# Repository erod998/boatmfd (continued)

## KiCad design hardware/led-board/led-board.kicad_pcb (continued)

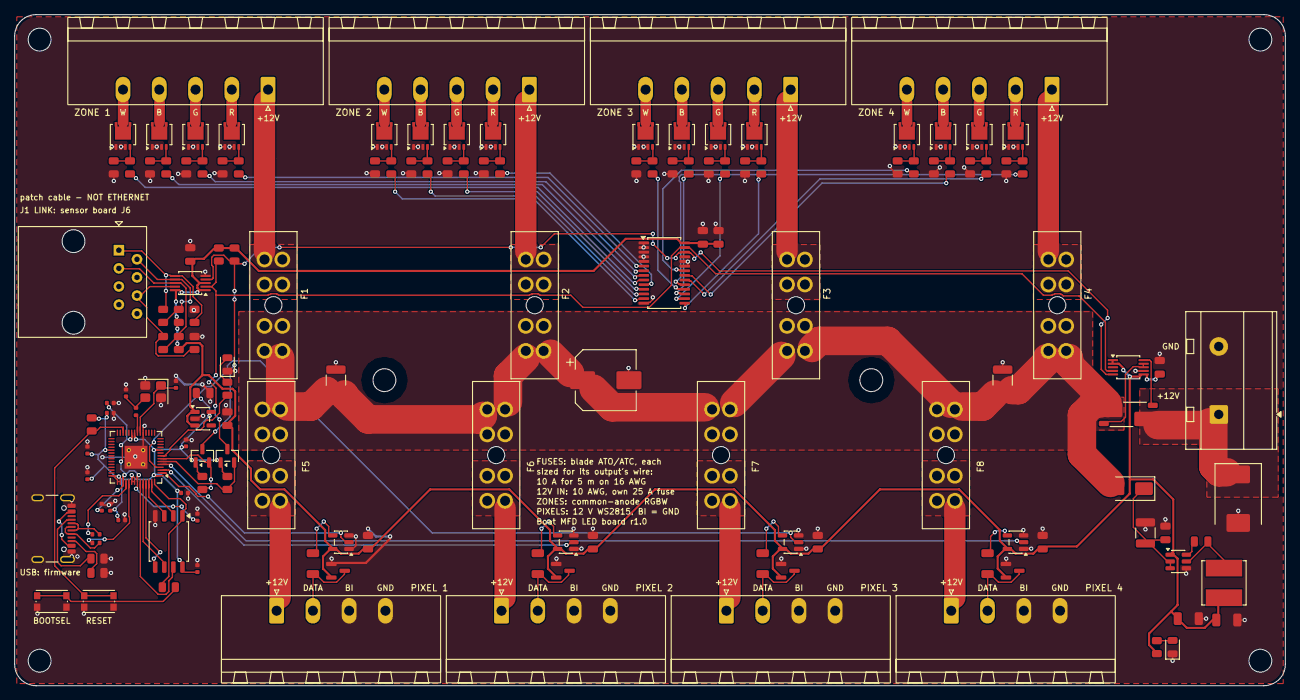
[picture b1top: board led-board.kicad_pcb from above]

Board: 2 copper layers, 178.0 x 94.0 mm, 153 parts (0 on the bottom side), 107 nets.

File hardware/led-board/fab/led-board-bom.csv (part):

Comment,Designator,Footprint,MPN,Qty,Mount,Note
100n,"C1,C5,C11,C12,C14,C15,C16,C17,C18",0805,CL21B104KBCNNNC,9,SMD,"U1 decoupling; U5 decoupling; U6 input, high frequency; U6 bootstrap; U7 decoupling; U8 decoupling; U9 decoupling; U10 decoupling; U4 decoupling"
22u,"C13,C19",1206,CL31A226KAHNNNE,2,SMD,U6 output
100n,"C20,C23,C24,C25,C26,C27,C28,C31,C32",0402,CL05B104KO5NNNC,9,SMD,"U3 decoupling; U2 IOVDD (pin 1); U2 IOVDD (pin 10); U2 IOVDD (pin 22); U2 IOVDD (pin 33); U2 IOVDD and ADC_AVDD (pins 42, 43); U2 USB_VDD and IOVDD (pins 48, 49); U2 DVDD (pin 23); U2 DVDD (pin 50)"
15p,"C21,C22",0402,CL05C150JB5NNNC,2,SMD,crystal load
1u,"C29,C30",0402,CL05A105KA5NQNC,2,SMD,U2 VREG_VIN (pin 44); U2 VREG_VOUT (pin 45): the 1.1 V core supply
10u,C34,0805,CL21A106KAYNNNE,1,SMD,"U11 output, the 3.3 V bulk"
1u,"C6,C33",0805,CL21B105KAFNNNE,2,SMD,U5 decoupling; U11 input
100u 35V,C7,CP,EEE-FK1V101P,1,SMD,"12 V bulk: the PWM's current steps, and damping for the feed wire"
10u,"C8,C9,C10",1210,CL32B106KBJNNNE,3,SMD,"12 V bypass, zone side; 12 V bypass, pixel side; U6 input (50 V)"
SMCJ18A,D1,SMC,SMCJ18A,1,SMD,1500 W surge clamp on the 12 V input (18 V stand-off)
SS14,D2,SMA,SS14,1,SMD,reverse polarity protection for the logic supply
BAT54S,"D3,D4,D5,D6",SOT-23,"BAT54S,215",4,SMD,clamps J7's data line between GND and 5 V; clamps J8's data line between GND and 5 V; clamps J9's data line between GND and 5 V; clamps J10's data line between GND and 5 V
green,D7,LED,LTST-C171GKT,1,SMD,lit when the board has 12 V
yellow,D8,LED,LTST-C171YKT,1,SMD,the RP2040's status: blinks while its firmware runs
USB,J11,USB_C_Receptacle_GCT_USB4105-xx-A_16P_TopMnt_Horizontal,GCT USB4105-GF-A,1,SMD,firmware loading only (VBUS unused: the board must have its 12 V)
6.8u,L1,L,SRN6045TA-6R8M,1,SMD,U6's inductor
BUK9M7R2-40E,"Q1,Q2,Q3,Q4,Q5,Q6,Q7,Q8,Q9,Q10,Q11,Q12,Q13,Q14,Q15,Q16",LFPAK33,BUK9M7R2-40EX,16,SMD,zone 1 R: PCA9685 output 0; zone 1 G: PCA9685 output 1; zone 1 B: PCA9685 output 2; zone 1 W: PCA9685 output 3; zone 2 R: PCA9685 output 4; zone 2 G: PCA9685 output 5; zone 2 B: PCA9685 output 6; zone 2 W: PCA9685 output 7; zone 3 R: PCA9685 output 8; zone 3 G: PCA9685 output 9; zone 3 B: PCA9685 output 10; zone 3 W: PCA9685 output 11; zone 4 R: PCA9685 output 12; zone 4 G: PCA9685 output 13; zone 4 B: PCA9685 output 14; zone 4 W: PCA9685 output 15
BSS138,"Q17,Q18",SOT-23,BSS138,2,SMD,"SDA level shift, 3.3 V to 5 V; SCL level shift, 3.3 V to 5 V"
100,"R1,R2,R3,R4,R5,R6,R7,R8,R9,R10,R11,R12,R13,R14,R15,R16",0805,RC0805FR-07100RL,16,SMD,gate resistor
47k,"R17,R18,R19,R20,R21,R22,R23,R24,R25,R26,R27,R28,R29,R30,R31,R32",0805,RC0805FR-0747KL,16,SMD,gate pull-down
620,"R33,R35,R36,R38",0805,RC0805FR-07620RL,4,SMD,link SCL pair: bias (pull-up); link SCL pair: bias (pull-down); link SDA pair: bias (pull-up); link SDA pair: bias (pull-down)
120,"R34,R37",0805,RC0805FR-07120RL,2,SMD,link SCL pair: termination; link SDA pair: termination
4.7k,"R39,R40",0805,RC0805FR-074K7L,2,SMD,"I2C pull-up, 5 V side"
10k,"R41,R42,R49",0805,RC0805FR-0710KL,3,SMD,"I2C pull-up, RP2040 side; RUN pull-up"
330,"R43,R44,R45,R46",1206,RC1206FR-07330RL,4,SMD,J7 data series resistor; J8 data series resistor; J9 data series resistor; J10 data series resistor
1m,R47,2512 (4-terminal),WSK25121L000FEA,1,SMD,"1 mOhm, 1 W, four-terminal: 20 A makes 20 mV and 0.4 W"
1k,R48,0402,RC0402FR-071KL,1,SMD,limits the crystal's drive
1k,"R50,R55",0805,RC0805FR-071KL,2,SMD,BOOTSEL button to the flash's chip select; status LED
27,"R51,R52",0402,RC0402FR-0727RL,2,SMD,USB series resistor
5.1k,"R53,R54",0805,RC0805FR-075K1L,2,SMD,USB-C: identifies the board as a device
2.2k,R56,0805,RC0805FR-072K2L,1,SMD,power LED
BOOTSEL,SW1,SW,KMR221GLFS,1,SMD,"held during reset: U2 starts as a USB drive, to load firmware"
RESET,SW2,SW,KMR221GLFS,1,SMD,resets U2
PCA9615DP,U1,TSSOP-10,"PCA9615DP,118",1,SMD,"differential I2C from the RJ45, back to plain I2C"
AP2112K-3.3,U11,SOT-23-5,AP2112K-3.3TRG1,1,SMD,3.3 V for the RP2040 and its flash
RP2040,U2,QFN-56-1EP,RP2040,1,SMD,runs the addressable outputs; I2C target at 0x30
W25Q16JV,U3,SOIC-8,W25Q16JVSSIQ,1,SMD,U2's program (2 MB QSPI flash)
INA226,U4,TSSOP-10,INA226AIDGSR,1,SMD,"the board's current and voltage, I2C address 0x45"
PCA9685PW,U5,TSSOP-28,"PCA9685PW,118",1,SMD,"16 PWM channels, I2C address 0x40"
AP63205,U6,TSOT-23-6,AP63205WU-7,1,SMD,"5 V for the logic, 2 A buck (about 100 mA used)"
74AHCT1G125,"U7,U8,U9,U10",SOT-23-5,SN74AHCT1G125DBVR,4,SMD,pixel output 1: 3.3 V data to 5 V; pixel output 2: 3.3 V data to 5 V; pixel output 3: 3.3 V data to 5 V; pixel output 4: 3.3 V data to 5 V
12MHz,Y1,3225-4Pin,ABM8-272-T3,1,SMD,"U2's clock: the crystal Raspberry Pi specify, with its 15 pF loads and 1k in XOUT"
ATO,"F1,F2,F3,F4,F5,F6,F7,F8",FuseHolder_Blade_ATO_Littelfuse_FLR_178.6165,"Littelfuse 178.6165.0002 (ATO/ATC holder, 30 A)",8,THT (hand solder),zone 1's fuse: a standard blade (ATO/ATC) fuse sized for the strip's wire -- 10 A for 5 m of RGBW on 16 AWG; zone 2's fuse: a standard blade (ATO/ATC) fuse sized for the strip's wire -- 10 A for 5 m of RGBW on 16 AWG; zone 3's fuse: a standard blade (ATO/ATC) fuse sized for the strip's wire -- 10 A for 5 m of RGBW on 16 AWG; zone 4's fuse: a standard blade (ATO/ATC) fuse sized for the strip's wire -- 10 A for 5 m of RGBW on 16 AWG; J7's fuse: a standard blade (ATO/ATC) fuse -- 10 A for 5 m of WS2815 on 16 AWG; J8's fuse: a standard blade (ATO/ATC) fuse -- 10 A for 5 m of WS2815 on 16 AWG; J9's fuse: a standard blade (ATO/ATC) fuse -- 10 A for 5 m of WS2815 on 16 AWG; J10's fuse: a standard blade (ATO/ATC) fuse -- 10 A for 5 m of WS2815 on 16 AWG
LINK,J1,RJ45_Amphenol_54602-x08_Horizontal,Amphenol 54602-908LF,1,THT (hand solder),to the sensor board's J6: a straight-through Cat5e/Cat6 patch cable. NOT Ethernet: never plug either end into a network switch or a PoE injector
PIXEL 4,J10,"PhoenixContact_MSTB_2,5_4-GF-5,08_1x04_P5.08mm_Horizontal_ThreadedFlange","Phoenix Contact 1776524 (MSTB 2,5/ 4-GF-5,08); plug 1778001 (MSTB 2,5/ 4-STF-5,08)",1,THT (hand solder),"12 V addressable strip (WS2815...): 1 +12V, 2 DATA, 3 BI (ground), 4 GND; 12 A per pin"
12V IN,J2,TerminalBlock_MetzConnect_Type703_RT10N02HGLU_1x02_P9.52mm_Horizontal,METZ CONNECT RT10N02HGLU,1,THT (hand solder),"the strips' 12 V, 20 A (the terminal is rated 24 A, 10 AWG), from its own 25 A fuse"
ZONE 1,J3,"PhoenixContact_MSTB_2,5_5-GF-5,08_1x05_P5.08mm_Horizontal_ThreadedFlange","Phoenix Contact 1776537 (MSTB 2,5/ 5-GF-5,08); plug 1778014 (MSTB 2,5/ 5-STF-5,08)",1,THT (hand solder),"RGBW strip, common anode: 1 +12V, 2 R, 3 G, 4 B, 5 W (PCA9685 outputs 0-3); 12 A per pin"
ZONE 2,J4,"PhoenixContact_MSTB_2,5_5-GF-5,08_1x05_P5.08mm_Horizontal_ThreadedFlange","Phoenix Contact 1776537 (MSTB 2,5/ 5-GF-5,08); plug 1778014 (MSTB 2,5/ 5-STF-5,08)",1,THT (hand solder),"RGBW strip, common anode: 1 +12V, 2 R, 3 G, 4 B, 5 W (PCA9685 outputs 4-7); 12 A per pin"
ZONE 3,J5,"PhoenixContact_MSTB_2,5_5-GF-5,08_1x05_P5.08mm_Horizontal_ThreadedFlange","Phoenix Contact 1776537 (MSTB 2,5/ 5-GF-5,08); plug 1778014 (MSTB 2,5/ 5-STF-5,08)",1,THT (hand solder),"RGBW strip, common anode: 1 +12V, 2 R, 3 G, 4 B, 5 W (PCA9685 outputs 8-11); 12 A per pin"
ZONE 4,J6,"PhoenixContact_MSTB_2,5_5-GF-5,08_1x05_P5.08mm_Horizontal_ThreadedFlange","Phoenix Contact 1776537 (MSTB 2,5/ 5-GF-5,08); plug 1778014 (MSTB 2,5/ 5-STF-5,08)",1,THT (hand solder),"RGBW strip, common anode: 1 +12V, 2 R, 3 G, 4 B, 5 W (PCA9685 outputs 12-15); 12 A per pin"
PIXEL 1,J7,"PhoenixContact_MSTB_2,5_4-GF-5,08_1x04_P5.08mm_Horizontal_ThreadedFlange","Phoenix Contact 1776524 (MSTB 2,5/ 4-GF-5,08); plug 1778001 (MSTB 2,5/ 4-STF-5,08)",1,THT (hand solder),"12 V addressable strip (WS2815...): 1 +12V, 2 DATA, 3 BI (ground), 4 GND; 12 A per pin"
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
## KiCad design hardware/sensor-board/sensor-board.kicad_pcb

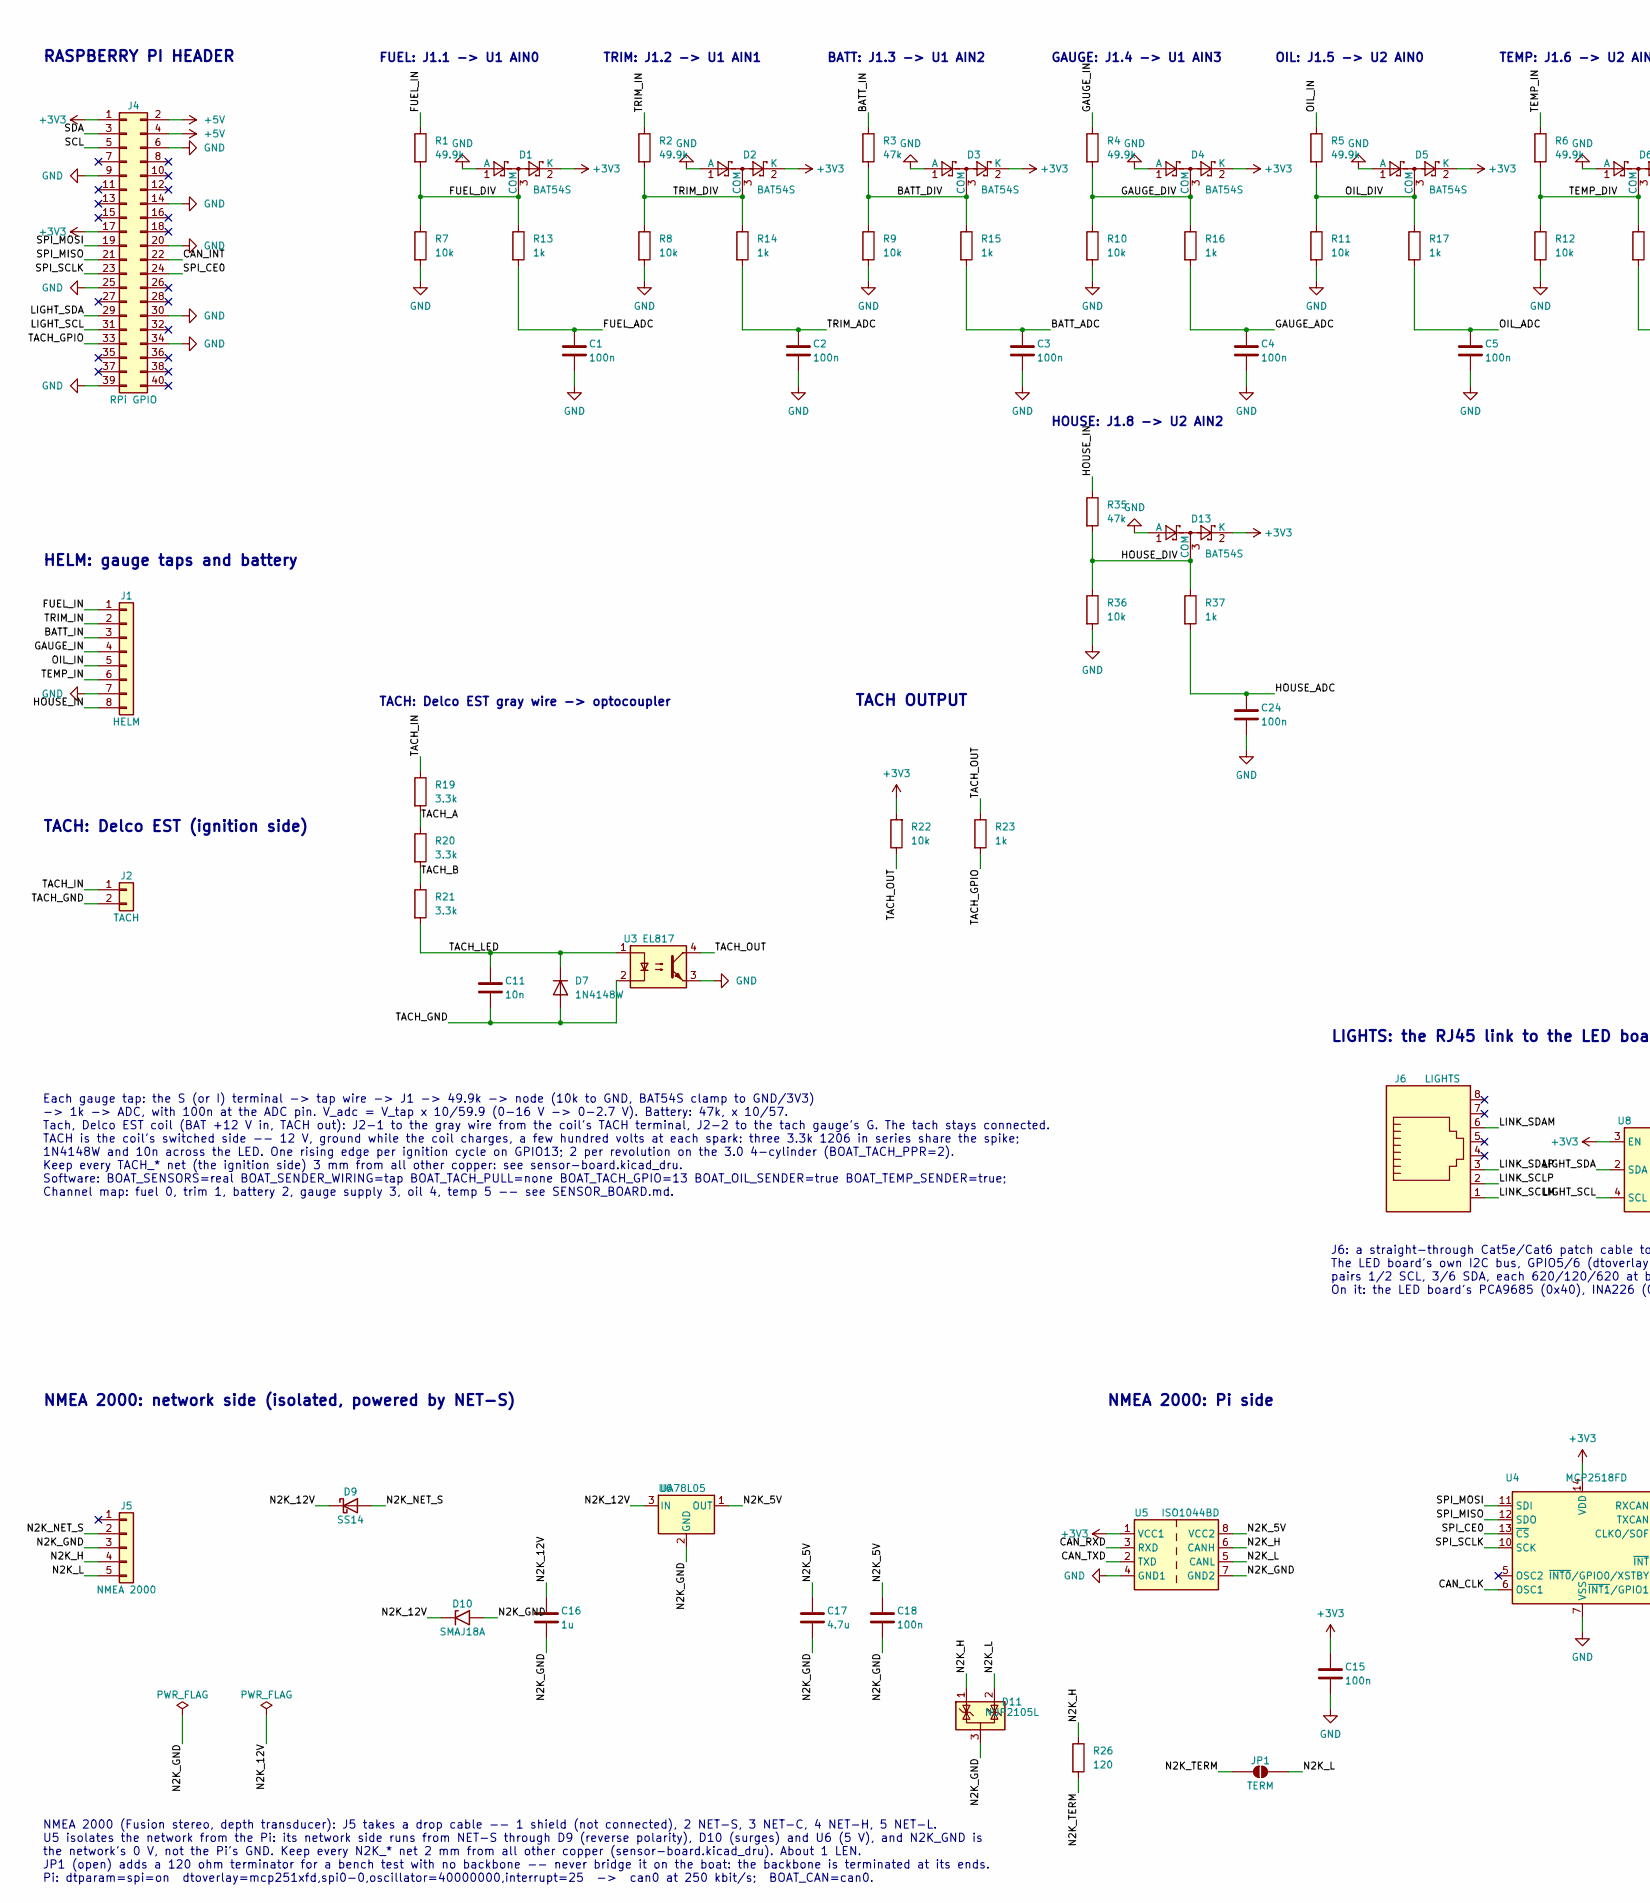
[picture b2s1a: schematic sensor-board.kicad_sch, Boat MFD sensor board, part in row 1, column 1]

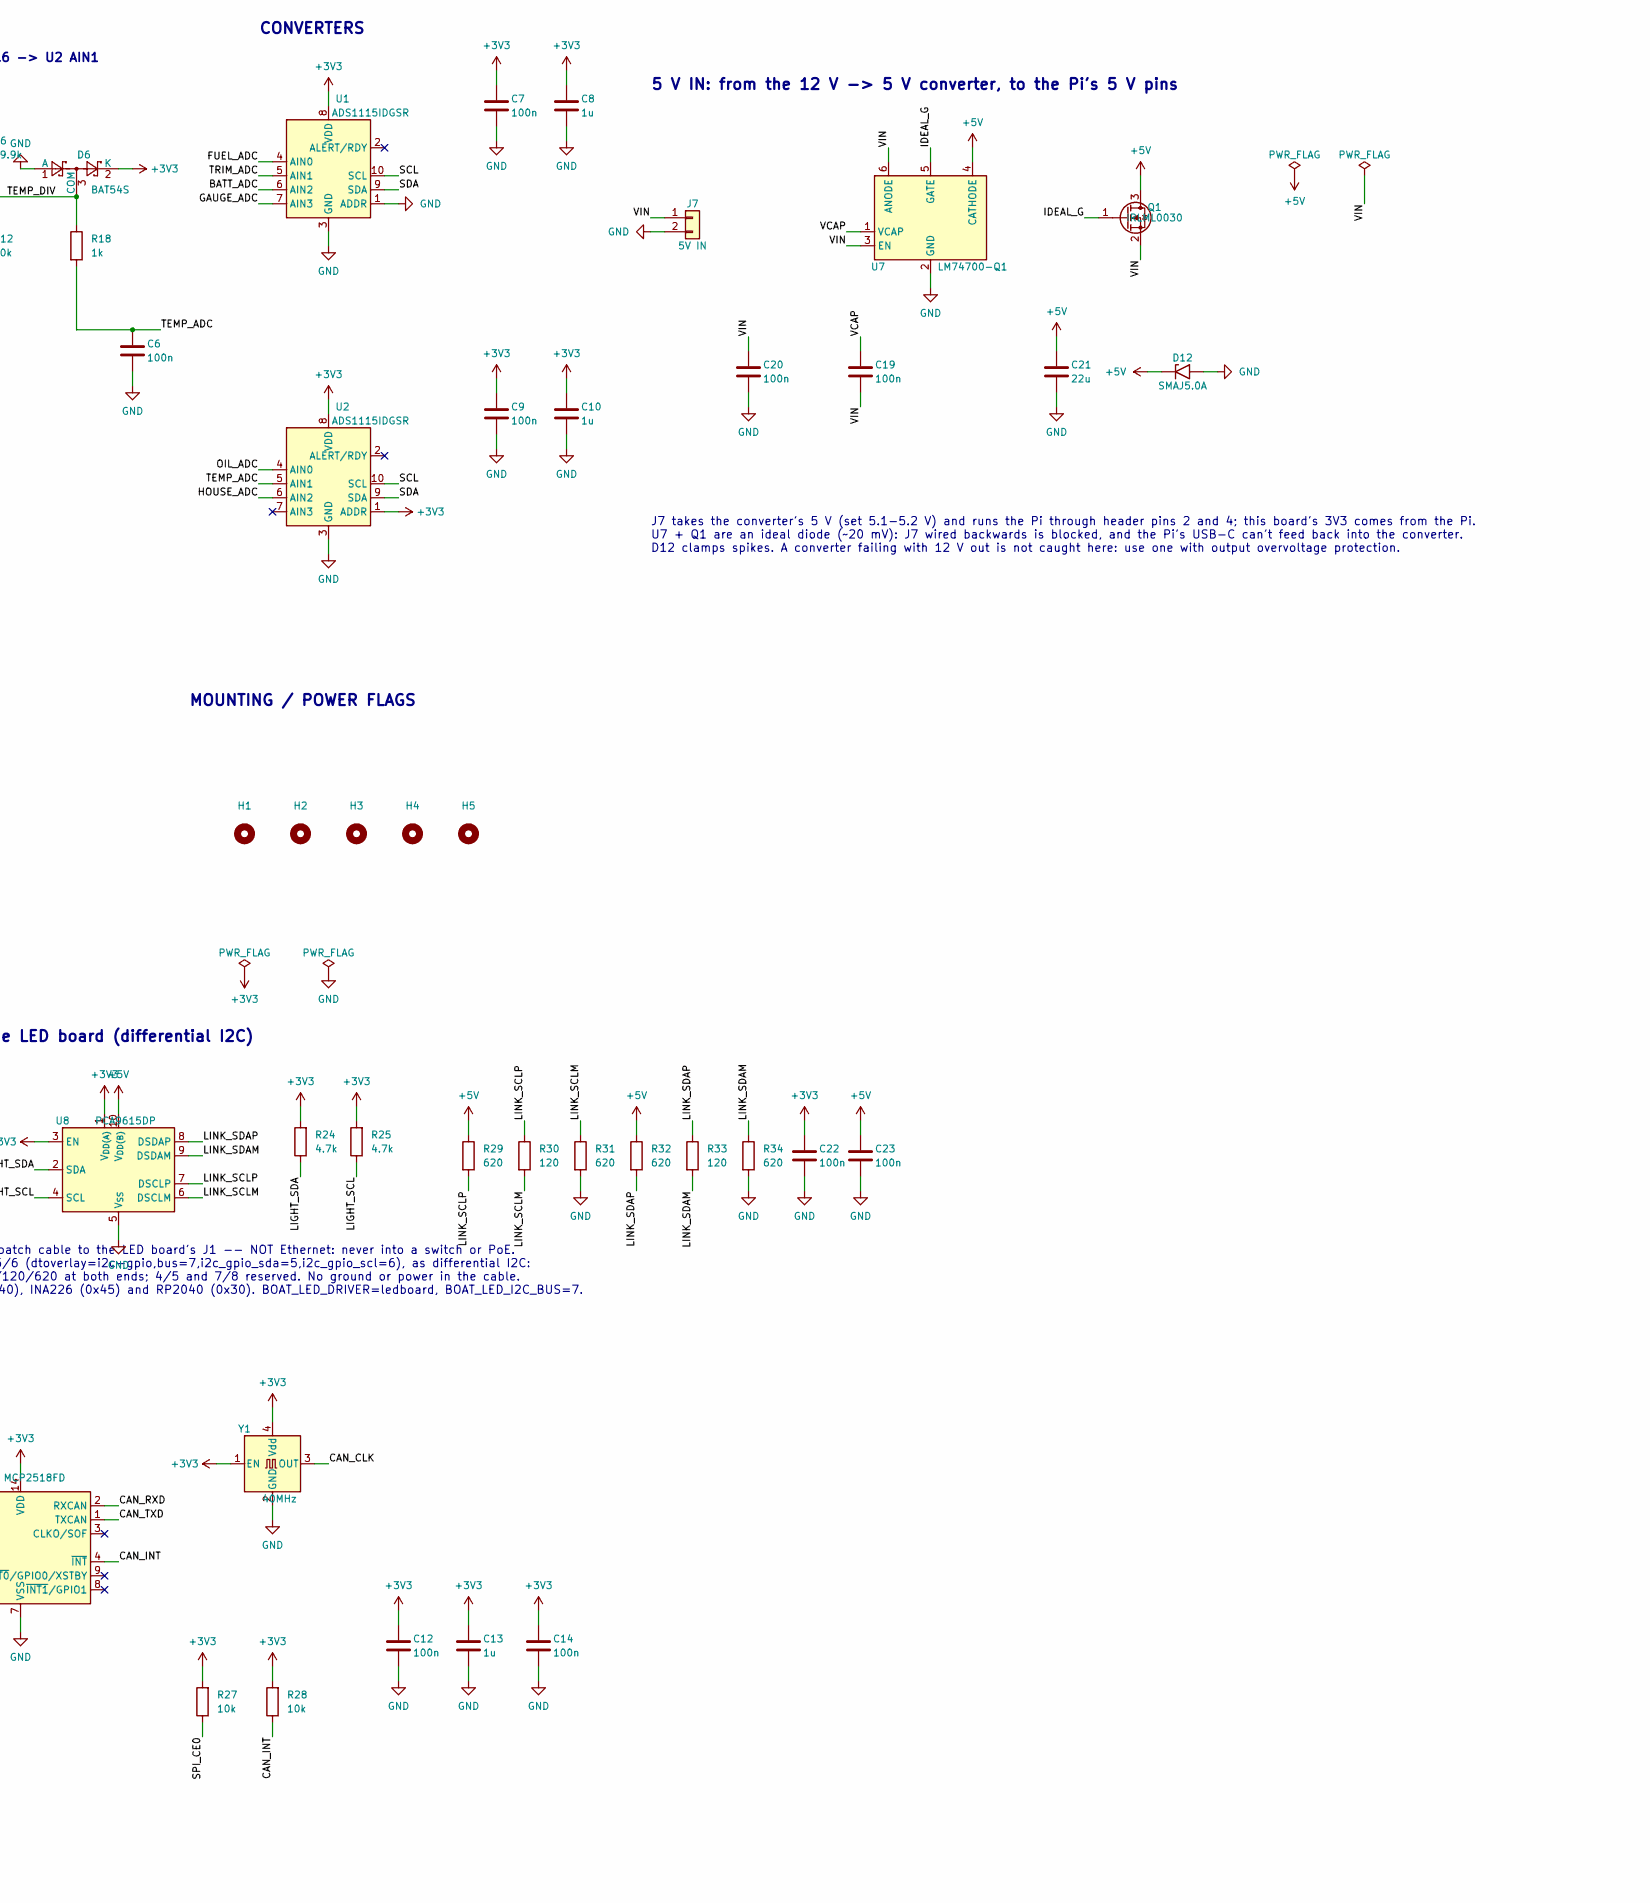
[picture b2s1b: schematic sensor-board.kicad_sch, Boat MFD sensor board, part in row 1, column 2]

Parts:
C1, C2, C3, C4, C5, C6, C7, C9, C12, C14, C15, C18, C19, C20, C24: 100n; C_0805_2012Metric_NoSilk; MPN CL21B104KBCNNNC
C8, C10, C13: 1u; C_0805_2012Metric_NoSilk; MPN CL21B105KAFNNNE
C11: 10n; C_0805_2012Metric_NoSilk; MPN CL21B103KBANNNC
C16: 1u; C_1206_3216Metric_NoSilk; MPN CL31B105KBHNNNE
C17: 4.7u; C_0805_2012Metric_NoSilk; MPN CL21A475KAQNNNE
C21: 22u; C_1206_3216Metric_NoSilk; MPN CL31A226KAHNNNE
C22, C23: 100n; C_0402_1005Metric_NoSilk; MPN CL05B104KO5NNNC
D1, D2, D3, D4, D5, D6, D13: BAT54S; SOT-23_NoSilk; MPN BAT54S,215
D7: 1N4148W; D_SOD-123; MPN 1N4148W-7-F
D9: SS14; D_SMA; MPN SS14
D10: SMAJ18A; D_SMA; MPN SMAJ18A
D11: NUP2105L; SOT-23_NoSilk; MPN NUP2105LT1G
D12: SMAJ5.0A; D_SMA; MPN SMAJ5.0A
H1, H2, H3, H4, H5: MountingHole; MountingHole_2.7mm_M2.5
J1: HELM; PhoenixContact_MC_1,5_8-GF-3.81_1x08_P3.81mm_Horizontal_Thr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; MPN Phoenix Contact 1827923 (MC 1,5/ 8-GF-3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
J2: TACH; PhoenixContact_MC_1,5_2-GF-3.81_1x02_P3.81mm_Horizontal_Thr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; MPN Phoenix Contact 1827868 (MC 1,5/ 2-GF-3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
J4: RPi GPIO; PinSocket_2x20_P2.54mm_Vertical; MPN 2x20 female stacking header, 2.54 mm, e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
J5: NMEA 2000; PhoenixContact_MC_1,5_5-GF-3.81_1x05_P3.81mm_Horizontal_Thr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; MPN Phoenix Contact 1827897 (MC 1,5/ 5-GF-3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
J6: LIGHTS; RJ45_Amphenol_54602-x08_Horizontal; MPN Amphenol 54602-908LF
J7: 5V IN; PhoenixContact_MC_1,5_2-GF-3.81_1x02_P3.81mm_Horizontal_Thr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; MPN Phoenix Contact 1827868 (MC 1,5/ 2-GF-3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
JP1: TERM; SolderJumper-2_P1.3mm_Open_RoundedPad1.0x1.5mm
Q1: IRLML0030; SOT-23; MPN IRLML0030TRPBF
R1, R2, R4, R5, R6: 49.9k; R_1206_3216Metric_NoSilk; MPN RC1206FR-0749K9L
R3, R35: 47k; R_1206_3216Metric_NoSilk; MPN RC1206FR-0747KL
R7, R8, R9, R10, R11, R12, R22, R27, R28, R36: 10k; R_0805_2012Metric_NoSilk; MPN RC0805FR-0710KL
R13, R14, R15, R16, R17, R18, R23, R37: 1k; R_0805_2012Metric_NoSilk; MPN RC0805FR-071KL
R19, R20, R21: 3.3k; R_1206_3216Metric_NoSilk; MPN RC1206FR-073K3L
R24, R25: 4.7k; R_0805_2012Metric_NoSilk; MPN RC0805FR-074K7L
R26: 120; R_0805_2012Metric_NoSilk; MPN RC0805FR-07120RL
R29, R31, R32, R34: 620; R_0402_1005Metric_NoSilk; MPN RC0402FR-07620RL
R30, R33: 120; R_0402_1005Metric_NoSilk; MPN RC0402FR-07120RL
U1, U2: ADS1115IDGSR; TSSOP-10_3x3mm_P0.5mm; MPN ADS1115IDGSR
U3: EL817; SMDIP-4_W9.53mm; MPN EL817S1(C)(TU)-F
U4: MCP2518FD; SOIC-14_3.9x8.7mm_P1.27mm; MPN MCP2518FDT-E/SL
U5: ISO1044BD; SOIC-8_3.9x4.9mm_P1.27mm; MPN ISO1044BDR
U6: UA78L05; SOT-89-3; MPN UA78L05ACPK
U7: LM74700-Q1; SOT-23-6; MPN LM74700QDBVRQ1
U8: PCA9615DP; TSSOP-10_3x3mm_P0.5mm; MPN PCA9615DP,118
Y1: 40MHz; Oscillator_SMD_Abracon_ASE-4Pin_3.2x2.5mm; MPN ASE-40.000MHZ-L-C-T

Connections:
+3V3: C7.1, C8.1, C9.1, C10.1, C12.1, C13.1, C14.1, C15.1, C22.1, D1.2 (K), D2.2 (K), D3.2 (K), D4.2 (K), D5.2 (K), D6.2 (K), D13.2 (K), J4.1, J4.17, R22.2, R24.2, R25.2, R27.2, R28.2, U1.8 (VDD), U2.1 (ADDR), U2.8 (VDD), U4.14 (VDD), U5.1 (VCC1), U8.1 (V_{DD(A)}), U8.3 (EN), Y1.1 (EN), Y1.4 (Vdd)
+5V: C21.1, C23.1, D12.1 (A1), J4.2, J4.4, Q1.3 (D), R29.1, R32.1, U7.4 (CATHODE), U8.10 (V_{DD(B)})
/BATT_ADC: C3.1, R15.2, U1.6 (AIN2)
/BATT_DIV: D3.3 (COM), R3.2, R9.1, R15.1
/BATT_IN: J1.3, R3.1
/CAN_CLK: U4.6 (OSC1), Y1.3 (OUT)
/CAN_INT: J4.22, R28.1, U4.4 (~INT)
/CAN_RXD: U4.2 (RXCAN), U5.3 (RXD)
/CAN_TXD: U4.1 (TXCAN), U5.2 (TXD)
/FUEL_ADC: C1.1, R13.2, U1.4 (AIN0)
/FUEL_DIV: D1.3 (COM), R1.2, R7.1, R13.1
/FUEL_IN: J1.1, R1.1
/GAUGE_ADC: C4.1, R16.2, U1.7 (AIN3)
/GAUGE_DIV: D4.3 (COM), R4.2, R10.1, R16.1
/GAUGE_IN: J1.4, R4.1
/HOUSE_ADC: C24.1, R37.2, U2.6 (AIN2)
/HOUSE_DIV: D13.3 (COM), R35.2, R36.1, R37.1
/HOUSE_IN: J1.8, R35.1
/IDEAL_G: Q1.1 (G), U7.5 (GATE)
/LIGHT_SCL: J4.31, R25.1, U8.4 (SCL)
/LIGHT_SDA: J4.29, R24.1, U8.2 (SDA)
/LINK_SCLM: J6.1, R30.2, R31.1, U8.6 (DSCLM)
/LINK_SCLP: J6.2, R29.2, R30.1, U8.7 (DSCLP)
/LINK_SDAM: J6.6, R33.2, R34.1, U8.9 (DSDAM)
/LINK_SDAP: J6.3, R32.2, R33.1, U8.8 (DSDAP)
/N2K_5V: C17.1, C18.1, U5.8 (VCC2), U6.1 (OUT)
/N2K_12V: C16.1, D9.1 (K), D10.1 (A1), U6.3 (IN)
/N2K_GND: C16.2, C17.2, C18.2, D10.2 (A2), D11.3 (A), J5.3, U5.7 (GND2), U6.2 (GND)
/N2K_H: D11.1 (K), J5.4, R26.1, U5.6 (CANH)
/N2K_L: D11.2 (K), J5.5, JP1.2 (B), U5.5 (CANL)
/N2K_NET_S: D9.2 (A), J5.2
/N2K_TERM: JP1.1 (A), R26.2
/OIL_ADC: C5.1, R17.2, U2.4 (AIN0)
/OIL_DIV: D5.3 (COM), R5.2, R11.1, R17.1
/OIL_IN: J1.5, R5.1
/SCL: J4.5, U1.10 (SCL), U2.10 (SCL)
/SDA: J4.3, U1.9 (SDA), U2.9 (SDA)
/SPI_CE0: J4.24, R27.1, U4.13 (~CS)
/SPI_MISO: J4.21, U4.12 (SDO)
/SPI_MOSI: J4.19, U4.11 (SDI)
/SPI_SCLK: J4.23, U4.10 (SCK)
/TACH_A: R19.2, R20.1
/TACH_B: R20.2, R21.1
/TACH_GND: C11.2, D7.2 (A), J2.2, U3.2
/TACH_GPIO: J4.33, R23.2
/TACH_IN: J2.1, R19.1
/TACH_LED: C11.1, D7.1 (K), R21.2, U3.1
/TACH_OUT: R22.1, R23.1, U3.4
/TEMP_ADC: C6.1, R18.2, U2.5 (AIN1)
/TEMP_DIV: D6.3 (COM), R6.2, R12.1, R18.1
/TEMP_IN: J1.6, R6.1
/TRIM_ADC: C2.1, R14.2, U1.5 (AIN1)
/TRIM_DIV: D2.3 (COM), R2.2, R8.1, R14.1
/TRIM_IN: J1.2, R2.1
/VCAP: C19.1, U7.1 (VCAP)
/VIN: C19.2, C20.1, J7.1, Q1.2 (S), U7.3 (EN), U7.6 (ANODE)
GND: C1.2, C2.2, C3.2, C4.2, C5.2, C6.2, C7.2, C8.2, C9.2, C10.2, C12.2, C13.2, C14.2, C15.2, C20.2, C21.2, C22.2, C23.2, C24.2, D1.1 (A), D2.1 (A), D3.1 (A), D4.1 (A), D5.1 (A), D6.1 (A), D12.2 (A2), D13.1 (A), J1.7, J4.6, J4.9, J4.14, J4.20, J4.25, J4.30, J4.34, J4.39, J7.2, R7.2, R8.2, R9.2, R10.2, R11.2, R12.2, R31.2, R34.2, R36.2, U1.1 (ADDR), U1.3 (GND), U2.3 (GND), U3.3, U4.7 (VSS), U5.4 (GND1), U7.2 (GND), U8.5 (V_{SS}), Y1.2 (GND)

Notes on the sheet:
FUEL: J1.1 -> U1 AIN0
TRIM: J1.2 -> U1 AIN1
BATT: J1.3 -> U1 AIN2
GAUGE: J1.4 -> U1 AIN3
OIL: J1.5 -> U2 AIN0
TEMP: J1.6 -> U2 AIN1
HOUSE: J1.8 -> U2 AIN2
TACH: Delco EST gray wire -> optocoupler
RASPBERRY PI HEADER
HELM: gauge taps and battery
TACH: Delco EST (ignition side)
CONVERTERS
TACH OUTPUT
MOUNTING / POWER FLAGS
LIGHTS: the RJ45 link to the LED board (differential I2C)
5 V IN: from the 12 V -> 5 V converter, to the Pi's 5 V pins
NMEA 2000: network side (isolated, powered by NET-S)
NMEA 2000: Pi side
Each gauge tap: the S (or I) terminal -> tap wire -> J1 -> 49.9k -> node (10k to GND, BAT54S clamp to GND/3V3) -> 1k -> ADC, with 100n at the ADC pin. V_adc = V_tap x 10/59.9 (0-16 V -> 0-2.7 V). Battery: 47k, x 10/57. Tach, Delco EST coil (BAT +12 V in, TACH out): J2-1 to the gray wire from the co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
NMEA 2000 (Fusion stereo, depth transducer): J5 takes a drop cable -- 1 shield (not connected), 2 NET-S, 3 NET-C, 4 NET-H, 5 NET-L. U5 isolates the network from the Pi: its network side runs from NET-S through D9 (reverse polarity), D10 (surges) and U6 (5 V), and N2K_GND is the network's 0 V, not t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
J6: a straight-through Cat5e/Cat6 patch cable to the LED board's J1 -- NOT Ethernet: never into a switch or PoE. The LED board's own I2C bus, GPIO5/6 (dtoverlay=i2c-gpio,bus=7,i2c_gpio_sda=5,i2c_gpio_scl=6), as differential I2C: pairs 1/2 SCL, 3/6 SDA, each 620/120/620 at both ends; 4/5 and 7/8 res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
J7 takes the converter's 5 V (set 5.1-5.2 V) and runs the Pi through header pins 2 and 4; this board's 3V3 comes from the Pi. U7 + Q1 are an ideal diode (~20 mV): J7 wired backwards is blocked, and the Pi's USB-C can't feed back into the converter. D12 clamps spikes. A converter failing with 12 V o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

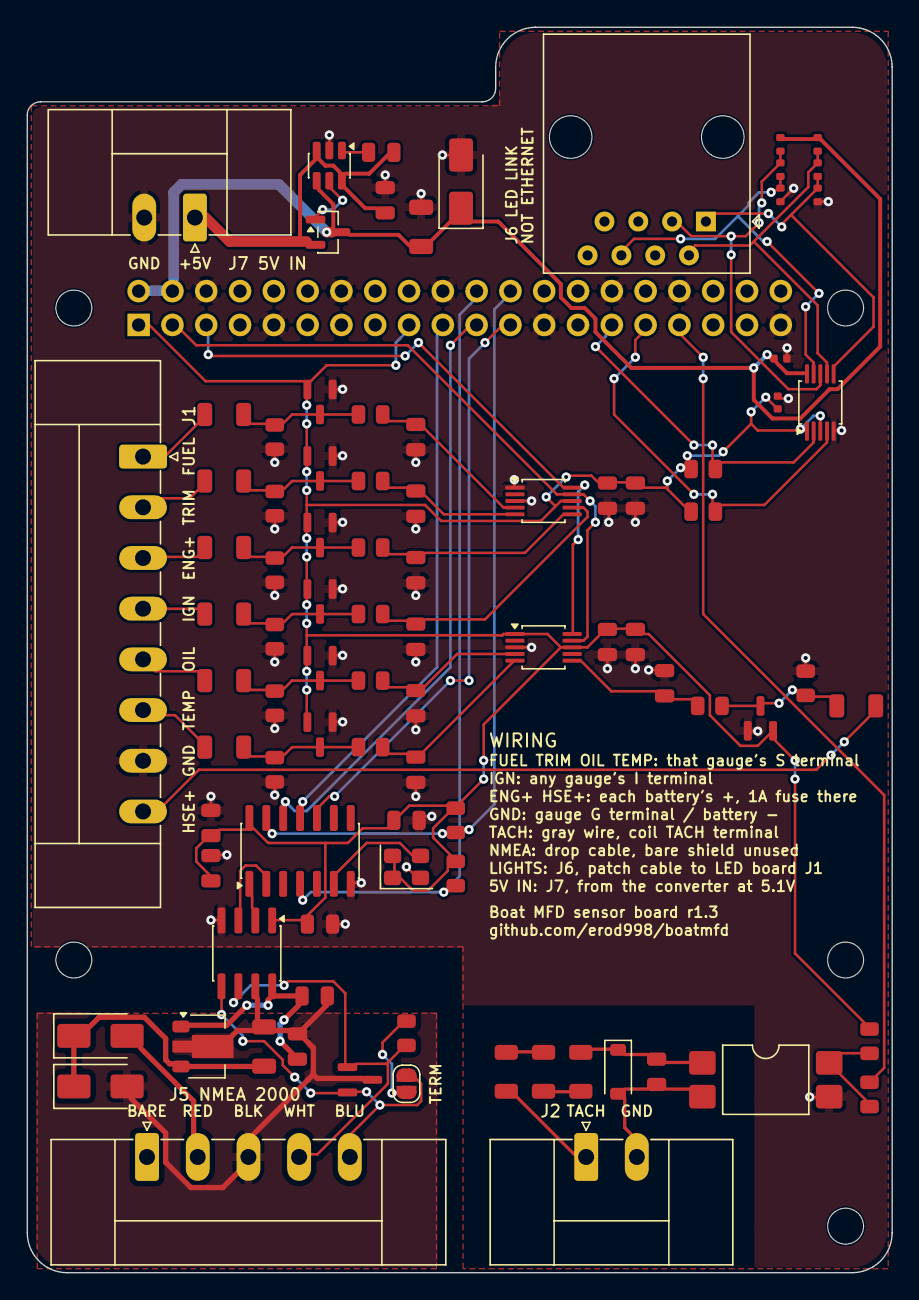
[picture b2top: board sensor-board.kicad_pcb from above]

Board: 2 copper layers, 65.0 x 93.6 mm, 95 parts (1 on the bottom side), 57 nets.

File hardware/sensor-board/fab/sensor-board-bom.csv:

Comment,Designator,Footprint,MPN,Qty,Mount,Note
100n,"C1,C2,C3,C4,C5,C6,C7,C9,C12,C14,C15,C18,C19,C20,C24",0805,CL21B104KBCNNNC,15,SMD,ADC input filter; U1 decoupling; U2 decoupling; U4 decoupling; Y1 decoupling; U5 Pi-side decoupling; U5 network-side decoupling; U7 charge pump (VCAP to ANODE); J7 input
10n,C11,0805,CL21B103KBANNNC,1,SMD,filters the ring-down after each spark
1u,C16,1206,CL31B105KBHNNNE,1,SMD,regulator input (50 V)
4.7u,C17,0805,CL21A475KAQNNNE,1,SMD,regulator output; U5's VCC2 bulk (TI: ~4.7 uF)
22u,C21,1206,CL31A226KAHNNNE,1,SMD,bulk at the Pi's 5 V pins
100n,"C22,C23",0402,CL05B104KO5NNNC,2,SMD,"U8 decoupling, 3.3 V side; U8 decoupling, cable side"
1u,"C8,C10,C13",0805,CL21B105KAFNNNE,3,SMD,U1 decoupling; U2 decoupling; U4 decoupling
BAT54S,"D1,D2,D3,D4,D5,D6,D13",SOT-23,"BAT54S,215",7,SMD,clamps the divider node between GND and 3V3
SMAJ18A,D10,SMA,SMAJ18A,1,SMD,clamps surges on the network's power
NUP2105L,D11,SOT-23,NUP2105LT1G,1,SMD,ESD and surge protection for NET-H / NET-L
SMAJ5.0A,D12,SMA,SMAJ5.0A,1,SMD,clamps spikes on the 5 V rail
1N4148W,D7,SOD-123,1N4148W-7-F,1,SMD,keeps the ring-down's negative swing off the LED
SS14,D9,SMA,SS14,1,SMD,reverse-polarity protection on NET-S
IRLML0030,Q1,SOT-23,IRLML0030TRPBF,1,SMD,"the ideal diode's switch: source to J7, drain to the Pi; 27 mOhm, VGS +/-20 V"
49.9k,"R1,R2,R4,R5,R6",1206,RC1206FR-0749K9L,5,SMD,tap top resistor (1206 for voltage rating)
1k,"R13,R14,R15,R16,R17,R18,R23,R37",0805,RC0805FR-071KL,8,SMD,ADC pin series resistor; protects the GPIO
3.3k,"R19,R20,R21",1206,RC1206FR-073K3L,3,SMD,tach input: 3 in series share the ignition spike
4.7k,"R24,R25",0805,RC0805FR-074K7L,2,SMD,"LED board I2C pull-up (SDA, GPIO5); LED board I2C pull-up (SCL, GPIO6)"
120,R26,0805,RC0805FR-07120RL,1,SMD,"bench terminator, only with JP1 bridged"
620,"R29,R31,R32,R34",0402,RC0402FR-07620RL,4,SMD,link SCL pair: bias (pull-up); link SCL pair: bias (pull-down); link SDA pair: bias (pull-up); link SDA pair: bias (pull-down)
47k,"R3,R35",1206,RC1206FR-0747KL,2,SMD,tap top resistor (1206 for voltage rating)
120,"R30,R33",0402,RC0402FR-07120RL,2,SMD,link SCL pair: termination; link SDA pair: termination
10k,"R7,R8,R9,R10,R11,R12,R22,R27,R28,R36",0805,RC0805FR-0710KL,10,SMD,divider bottom; opto pull-up; keeps U4 deselected while the Pi boots; interrupt pull-up
ADS1115IDGSR,"U1,U2",TSSOP-10,ADS1115IDGSR,2,SMD,"I2C 0x48: fuel, trim, battery, gauge supply; I2C 0x49: oil, engine temperature, house battery"
EL817,U3,SMDIP-4,EL817S1(C)(TU)-F,1,SMD,isolates the Pi from the ignition
MCP2518FD,U4,SOIC-14,MCP2518FDT-E/SL,1,SMD,SPI CAN FD controller (pin-for-pin successor to the MCP2517FD; Linux driver mcp251xfd)
ISO1044BD,U5,SOIC-8,ISO1044BDR,1,SMD,isolated CAN transceiver: the Pi side and the network side share no ground
UA78L05,U6,SOT-89-3,UA78L05ACPK,1,SMD,"5 V for U5's network side, from NET-S"
LM74700-Q1,U7,SOT-23-6,LM74700QDBVRQ1,1,SMD,"ideal diode controller: ANODE/EN to J7, CATHODE to the Pi's 5 V"
PCA9615DP,U8,TSSOP-10,"PCA9615DP,118",1,SMD,"the LED board's I2C bus (GPIO5/6, 3.3 V) as differential I2C (5 V) on the RJ45"
40MHz,Y1,3.2x2.5mm,ASE-40.000MHZ-L-C-T,1,SMD,U4's clock (oscillator=40000000 in the overlay)
HELM,J1,"PhoenixContact_MC_1,5_8-GF-3.81_1x08_P3.81mm_Horizontal_ThreadedFlange","Phoenix Contact 1827923 (MC 1,5/ 8-GF-3,81); plug 1827761 (MC 1,5/ 8-STF-3,81)",1,THT (hand solder),FUEL/TRIM/OIL/TEMP: that gauge's S terminal; ENG+ / HSE+: the engine / house battery's + terminal (1 A fuse at the battery); IGN: any gauge's I terminal; GND: gauge G / battery -
TACH,J2,"PhoenixContact_MC_1,5_2-GF-3.81_1x02_P3.81mm_Horizontal_ThreadedFlange","Phoenix Contact 1827868 (MC 1,5/ 2-GF-3,81); plug 1827703 (MC 1,5/ 2-STF-3,81)",1,THT (hand solder),TACH: the gray wire (EST coil TACH terminal); GND: the tach gauge's G terminal
RPi GPIO,J4,PinSocket_2x20_P2.54mm_Vertical,"2x20 female stacking header, 2.54 mm, extra-tall (e.g. Adafruit 1979)",1,THT (hand solder),to the Raspberry Pi
NMEA 2000,J5,"PhoenixContact_MC_1,5_5-GF-3.81_1x05_P3.81mm_Horizontal_ThreadedFlange","Phoenix Contact 1827897 (MC 1,5/ 5-GF-3,81); plug 1827732 (MC 1,5/ 5-STF-3,81)",1,THT (hand solder),"NMEA 2000 drop cable, Micro-C order: 1 shield (bare, not connected), 2 NET-S red, 3 NET-C black, 4 NET-H white, 5 NET-L blue"
LIGHTS,J6,RJ45_Amphenol_54602-x08_Horizontal,Amphenol 54602-908LF,1,THT (hand solder),to the LED board's J1: a straight-through Cat5e/Cat6 patch cable. NOT Ethernet: never plug either end into a network switch or a PoE injector
5V IN,J7,"PhoenixContact_MC_1,5_2-GF-3.81_1x02_P3.81mm_Horizontal_ThreadedFlange","Phoenix Contact 1827868 (MC 1,5/ 2-GF-3,81); plug 1827703 (MC 1,5/ 2-STF-3,81)",1,THT (hand solder),"from the 12 V -> 5 V converter (set 5.1-5.2 V, 3 A): 1 +5V, 2 GND"

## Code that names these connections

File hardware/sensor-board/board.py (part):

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    "R27": (32.2, 42.0, 90, "F"), "R28": (32.2, 46.0, 90, "F"),
    # Lights: the RJ45 on its tab, facing up, the pairs' terminations beside its pins 1-3 (0402s:
    # the tab is 10 mm wide there), and the differential-I2C buffer below the mounting hole, on
    # the way to GPIO5/6. The bus's pull-ups stay by the header.
    "J6": (51.0, -3.0, 180, "F"),
    "U8": (59.6, 10.6, 90, "F"), "C22": (56.4, 10.6, 90, "F"), "C23": (56.6, 7.3, 0, "F"),
    # Each pair's terminations in a chain down the tab: 5 V, 620, P, 120, M, 620, GND.
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         [f"{n}_{s}" for n, *_ in design.CHANNELS if n != "HOUSE" for s in ("IN", "DIV", "ADC")] +
         ["SDA", "SCL",
          "CAN_INT", "SPI_CE0", "SPI_MOSI", "SPI_MISO", "SPI_SCLK",
          "TACH_OUT", "TACH_GPIO", "LIGHT_SDA", "LIGHT_SCL",
          # the house battery's input crosses the board from J1.8: after everything it could wall off
          "HOUSE_DIV", "HOUSE_ADC", "HOUSE_IN", "+3V3"])
# The SPI bus runs the length of the board, from the header down to the CAN controller, across
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
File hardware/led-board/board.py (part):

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    "R37": (20.8, 46.0, 90), "R36": (23.0, 46.0, 90), "R38": (25.2, 46.0, 90),
    "R39": (28.6, 33.6, 90), "R40": (30.8, 33.6, 90),
    "Q18": (26.3, 61.8, 90), "Q17": (29.8, 61.8, 90), "R42": (26.3, 65.6, 90), "R41": (29.8, 65.6, 90),
    # The RP2040, turned so its GPIO0-6 face right (the I2C up to the level shift, the pixel data
    # down to its channel), its USB and flash pins down, its crystal up.
    "U2": (17.0, 62.0, 180),
    "Y1": (19.4, 52.8, 180), "R48": (17.0, 55.6, 90), "C21": (22.6, 51.8, 90), "C22": (15.6, 53.0, 90),
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         [f"PIX{n}_5V" for n in range(1, design.PIXELS + 1)] + [f"P{n}_DATA" for n in range(1, design.PIXELS + 1)] +
         [f"G{ch}" for ch in range(16)] + [f"PWM{ch}" for ch in range(16)])
# The RP2040's supplies drop to the bottom layer at its pins: on top, a supply joining two pins
# on one side would run across the signal pins between them and shut them in.
PREFER_BOTTOM = {"+1V1", "+3V3"}
# ...and the long signal runs, the pixel data along the bottom channel and the PWM along the top
# one: the strips' current (top layer only) crosses both channels, and underneath is clear.
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        """A straight stub from every connected pin of a quad package, before anything is routed
        round it: outward for the signals, and inward for the supplies, whose vias go in the ring
        between the pins and the exposed pad -- the bottom layer takes the supplies out under the
        chip. With every pin's way claimed, no track can run along a row of pins and shut the ones
        behind it in, and no supply via sits in a signal's way out."""
        x, y, _ = PLACE[ref]
        self.recording = self.stubs
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        if rest:
            print("  (not in ORDER, routed last:", ", ".join(rest) + ")")
        for net in ORDER + rest:
            if net == "ISENSE_P":         # ground pins the tracks after this would box in: U4 (between its sense pins), D8 (SDA/SCL)
                self.stitch_gnd(refs={"U4", "D8"})
            if net == "LINK_SDAP":        # U1's 5 V enable pin sits between SDA and SCL: its via first
                self.via_out("U1", {"+5V"})
            if net == "+5V":              # U5's right-hand PWM pins: their vias before the I2C runs past them
                self.via_out("U5", {f"PWM{ch}" for ch in range(8, 16)})
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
